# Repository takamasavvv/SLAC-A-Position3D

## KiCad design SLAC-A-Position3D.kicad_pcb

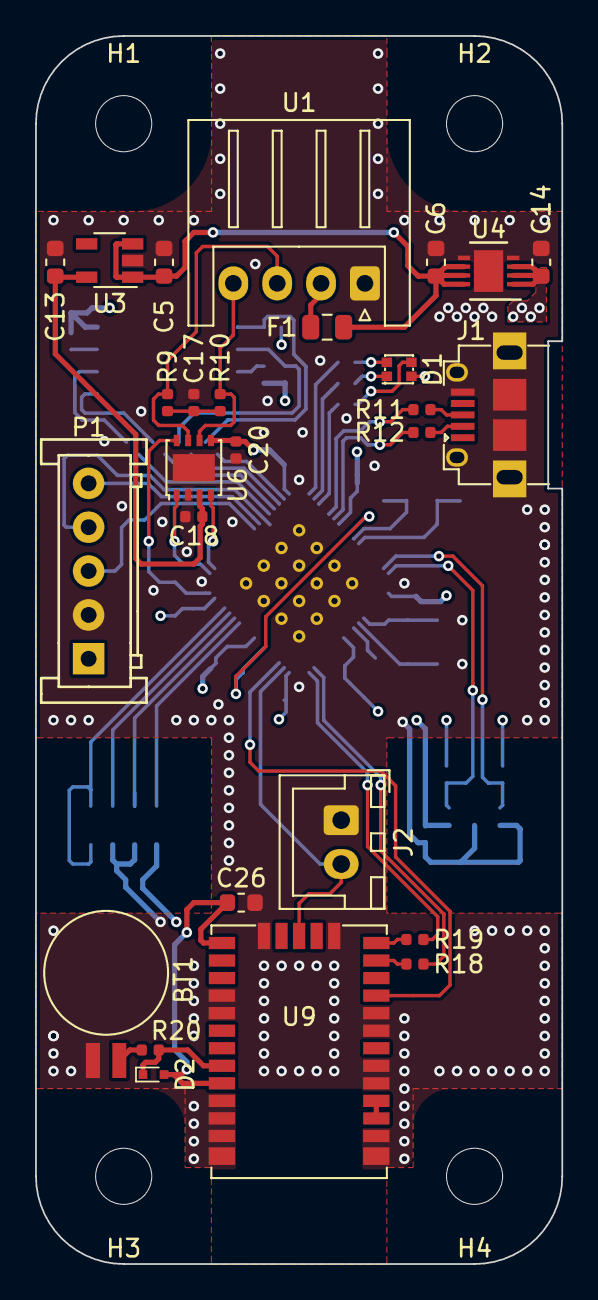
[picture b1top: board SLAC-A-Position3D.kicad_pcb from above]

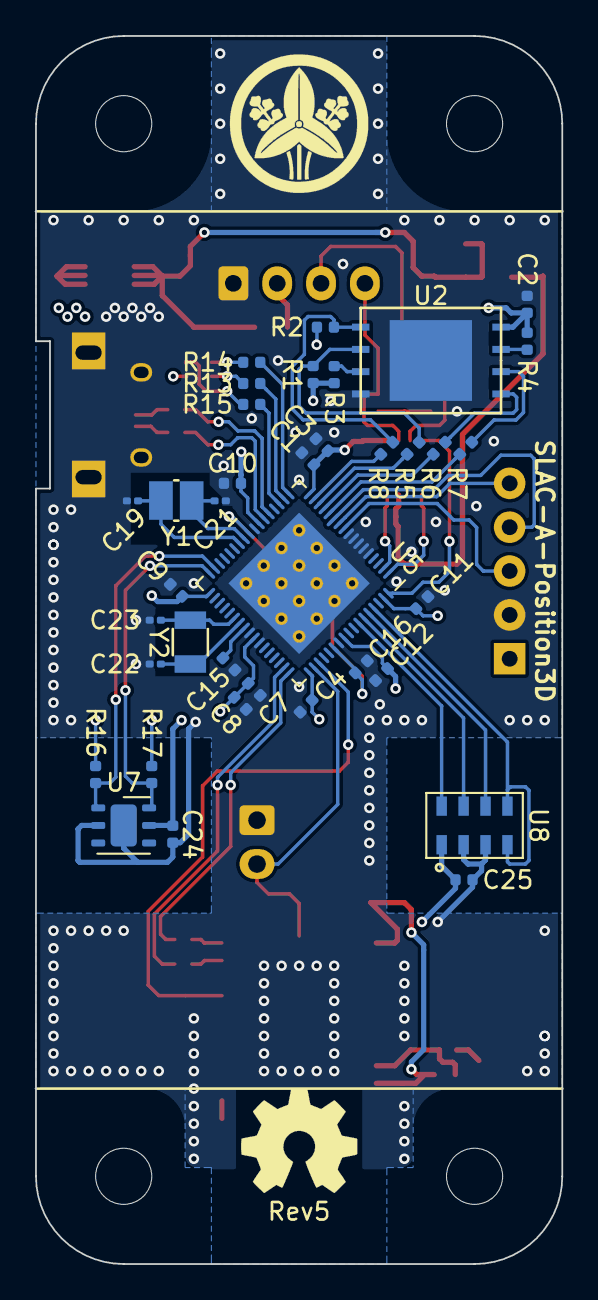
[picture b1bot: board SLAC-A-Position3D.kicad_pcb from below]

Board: 4 copper layers, 30.0 x 70.0 mm, 68 parts (37 on the bottom side), 55 nets.

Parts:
BT1: Battery_Cell; BatteryHolder_Seiko_MS621F
C1, C2, C3, C4, C7, C8, C9, C11, C18, C20, C24, C25: 0.1uF; C_0402_1005Metric
C5, C6, C13, C14: 10uF; C_0603_1608Metric
C10, C12, C15, C16: 1uF; C_0402_1005Metric
C17: 4.7nF; C_0402_1005Metric
C19, C21, C22, C23: 9pF; C_0201_0603Metric
C26: 4.7uF; C_0603_1608Metric
D1: LED_RGBA; LED_LiteOn_LTST-C19HE1WT
D2: D; D_SOD-723
F1: Polyfuse; Fuse_0805_2012Metric
H1, H2, H3, H4: MountingHole; MountingHole_3.2mm_M3
J1: USB_B_Micro; Hirose_ZX_ZX62D-B-5P8
J2: Conn_01x02; JST_XH_B2B-XH-A_1x02_P2.50mm_Vertical
P1: KRC_Conn_SWD; JST_JQ_05JQ-BT_1x05_P2.5mm_Vertical
R1, R2, R3, R4, R16, R17: 4.7kΩ; R_0402_1005Metric
R5, R6, R7, R8, R11, R12, R18, R19: 22Ω; R_0402_1005Metric
R9, R10: 56Ω; R_0402_1005Metric
R13: 1.5kΩ; R_0402_1005Metric
R14, R15: 820Ω; R_0402_1005Metric
R20: 68kΩ; R_0402_1005Metric
U1: KRC_Conn_CAN; JST_XH_S4B-XH-A_1x04_P2.50mm_Horizontal
U2: W25N01GVxxIG-IT; WSON-8_8x6mm_P1.27mm
U3: LT1761-5; TSOT-23-5
U4: LT1965xDD-3.3; DFN-8-1EP_3x3mm_P0.5mm_EP1.66x2.38mm
U5: CY8C58xxLTI-LPxxx; Cypress_QFN-68_EP_8x8_Pitch0.4mm
U6: NCV7342; DFN-8-1EP_3x3mm_P0.65mm_EP1.55x2.4mm
U7: HTU21D; DFN-6-1EP_3x3mm_P1mm_EP1.5x2.4mm
U8: MS5611; TE_Sensor_MS8607
U9: CAM-M8C; ublox-CAM
Y1: Crystal_MHz; Crystal_Murata_XRCHA
Y2: Crystal_kHz; Crystal_SeikoEpson_FC-135

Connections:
+3V3: C1.1, C2.1, C3.1, C4.1, C7.1, C8.1, C9.1, C10.1, C11.1, C12.1, C14.1, C20.1, C24.2, C25.2, C26.2, D1.4, D2.2, R1.1, R2.1, R3.1, R4.1, R16.2, R17.2, U2.8, U4.1, U4.2, U4.3, U5.17, U5.24, U5.35, U5.44, U5.52, U5.59, U5.67, U6.5, U7.5, U8.1, U9.1, U9.9
+5V: C13.1, C18.2, U3.5, U6.3
/CAN-RXD: U5.2, U6.4
/CAN-STB: U5.68, U6.8
/CAN-TXD: U5.1, U6.1
/Crystal_kHz_XI: C22.2, U5.41, Y2.1
/Crystal_kHz_XO: C23.2, U5.40, Y2.2
/Flash-MISO: R5.2, U5.15
/Flash-MOSI: R6.2, U5.14
/Flash-SCLK: R7.2, U5.13
/Flash-~CS: R8.2, U5.16
/GNSS-1PPS: J2.2, U5.53, U9.29
/GNSS-RXD: R19.2, U5.51
/GNSS-TXD: R18.2, U5.50
/GNSS-~RESET: U5.54, U9.23
/H-SCL: R17.1, U5.34, U7.6
/H-SDA: R16.1, U5.33, U7.1
/LED-B: R15.2, U5.20
/LED-G: R14.2, U5.18
/LED-R: R13.2, U5.19
/PT-MISO: U5.64, U8.6
/PT-MOSI: U5.63, U8.7
/PT-SCLK: U5.62, U8.8
/PT-~CS: U5.65, U8.4, U8.5
GND: BT1.2, C1.2, C2.2, C3.2, C4.2, C5.2, C6.2, C7.2, C8.2, C9.2, C10.2, C11.2, C12.2, C13.2, C14.2, C15.1, C16.1, C17.2, C18.1, C19.2, C20.2, C21.2, C22.1, C23.1, C24.1, C25.1, C26.1, J1.5, J1.6, J2.1, P1.2, U1.1, U2.4, U2.9, U3.2, U4.4, U4.5, U4.9, U5.5, U5.6, U5.7, U5.8, U5.9, U5.25, U5.43, U5.45, U5.58, U5.69, U6.2, U6.9, U7.2, U7.7, U8.2, U8.3, U9.4, U9.5, U9.10, U9.11, U9.12, U9.13, U9.14, U9.15, U9.18, U9.19, U9.21, U9.22, U9.27, U9.31
unnamed: BT1.1, R20.1
unnamed: C5.1, C6.1, F1.1, U3.1, U3.3, U4.6, U4.7, U4.8
unnamed: C15.2, U5.42
unnamed: C16.2, U5.26, U5.57
unnamed: C17.1, R9.2, R10.1
unnamed: C19.1, U5.28, Y1.1
unnamed: C21.1, U5.27, Y1.2
unnamed: D1.1, R13.1
unnamed: D1.2, R14.1
unnamed: D1.3, R15.1
unnamed: D2.1, R20.2, U9.8
unnamed: F1.2, U1.2
unnamed: J1.2, R12.1
unnamed: J1.3, R11.1
unnamed: P1.3, U5.10
unnamed: P1.4, U5.12
unnamed: P1.5, U5.11
unnamed: R1.2, R5.1, U2.2
unnamed: R2.2, R8.1, U2.1
unnamed: R3.2, U2.3
unnamed: R4.2, U2.7
unnamed: R6.1, U2.5
unnamed: R7.1, U2.6
unnamed: R9.1, U1.3, U6.7
unnamed: R10.2, U1.4, U6.6
unnamed: R11.2, U5.22
unnamed: R12.2, U5.23
unnamed: R18.1, U9.25
unnamed: R19.1, U9.26
unnamed: U9.16, U9.17

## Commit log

2020-02-02 complete rev 5 (redesign to 4 layer)
